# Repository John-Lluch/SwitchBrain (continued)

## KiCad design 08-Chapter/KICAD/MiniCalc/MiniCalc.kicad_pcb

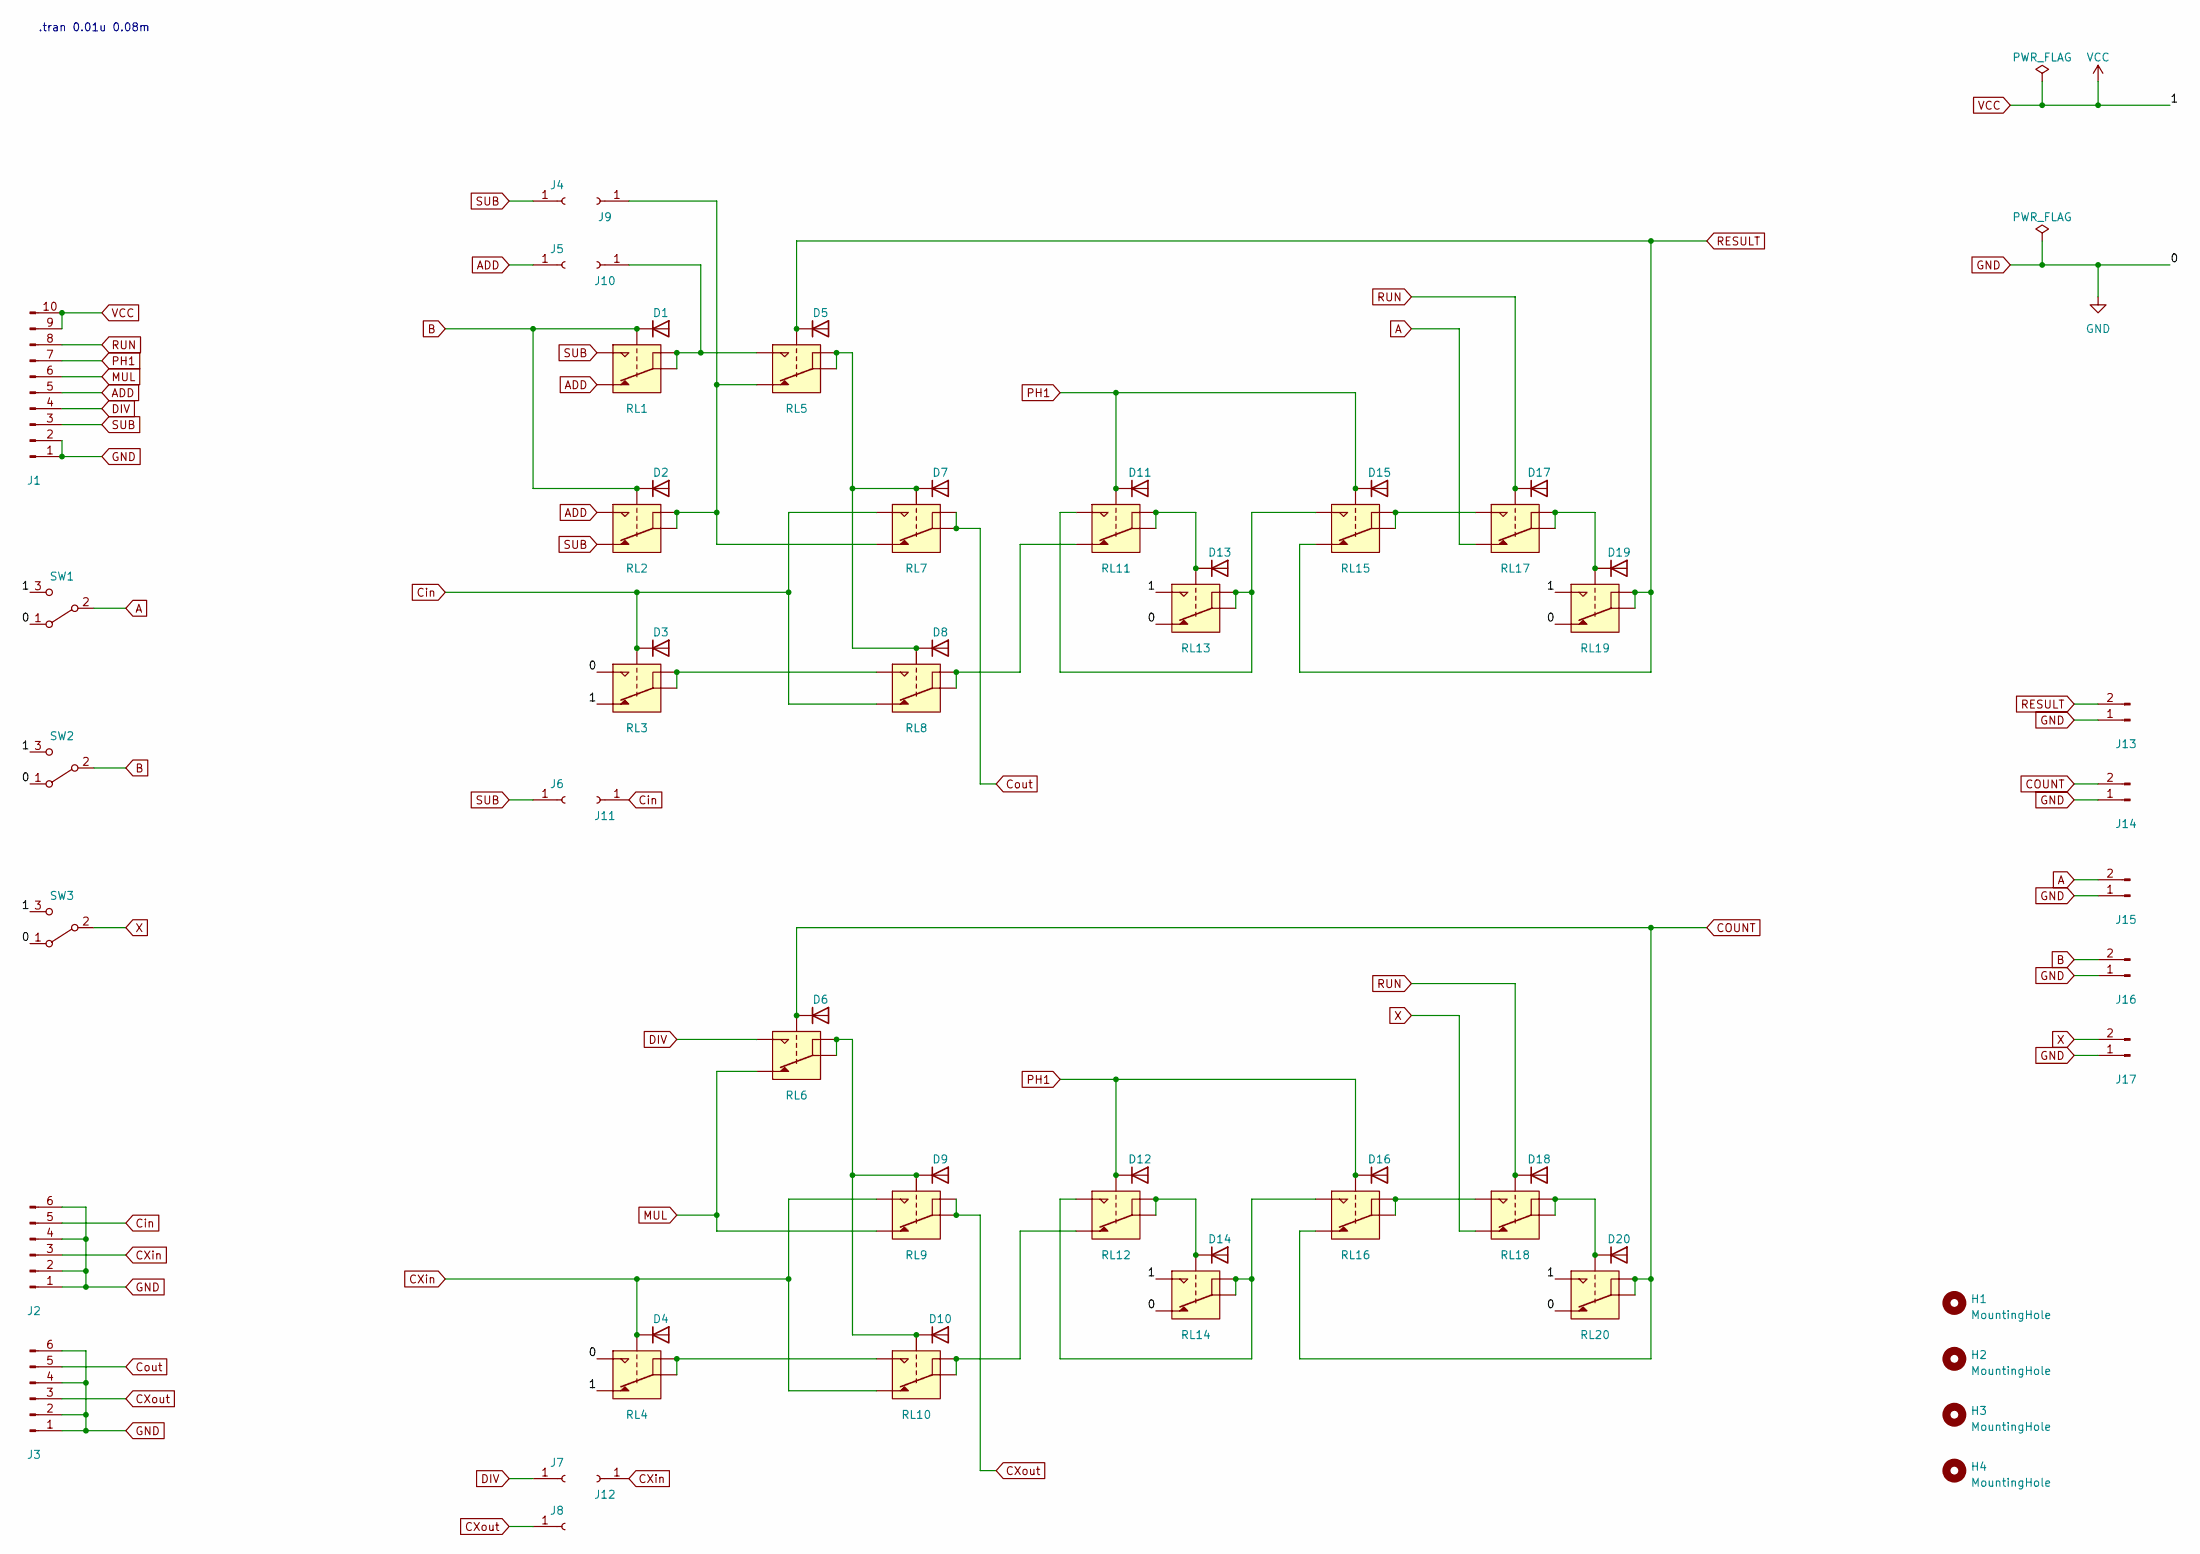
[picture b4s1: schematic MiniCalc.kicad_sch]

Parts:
D1, D2, D3, D4, D5, D6, D7, D8, D9, D10, D11, D12, D13, D14, D15, D16, D17, D18, D19, D20: 1N4007_FLYB; D_A-405_P2.54mm_Vertical_KathodeUp
H1, H2, H3, H4: MountingHole; MountingHole_3.2mm_M3_DIN965_Pad
J1: Conn_01x10_Pin; IDC-Header_2x05_P2.54mm_Horizontal
J2, J3: Conn_01x06_Pin; IDC-Header_2x03_P2.54mm_Horizontal
J4, J5, J6, J7, J8, J9, J10, J11, J12: Conn_01x01_Socket; Pin_D0.7mm_L6.5mm_W1.8mm_FlatFork
J13, J14, J15, J16, J17: Conn_01x02_Pin; JST_XH_S2B-XH-A_1x02_P2.50mm_Horizontal
RL1, RL2, RL3, RL4, RL5, RL6, RL7, RL8, RL9, RL10, RL11, RL12, RL13, RL14, RL15, RL16, RL17, RL18, RL19, RL20: G5V-1; Relay_SPDT_Omron_G5V-1_girat
SW1, SW2, SW3: SW_SPDT; SW_Toggle_SPDT_Horizontal

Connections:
A: J15.2, RL17.1, SW1.2 (B)
ADD: J1.5, J5.1, RL1.1, RL2.10
B: D1.1, D2.1, J16.2, RL1.9, RL2.9, SW2.2 (B)
COUNT: D6.1, J14.2, RL6.9, RL16.1, RL20.5, RL20.6
CXin: D4.1, J2.3, J12.1, RL4.9, RL9.10, RL10.1
CXout: J3.3, J8.1, RL9.5, RL9.6
Cin: D3.1, J2.5, J11.1, RL3.9, RL7.10, RL8.1
Cout: J3.5, RL7.5, RL7.6
DIV: J1.4, J7.1, RL6.10
GND: D1.2 (GND), D2.2 (GND), D3.2 (GND), D4.2 (GND), D5.2 (GND), D6.2 (GND), D7.2 (GND), D8.2 (GND), D9.2 (GND), D10.2 (GND), D11.2 (GND), D12.2 (GND), D13.2 (GND), D14.2 (GND), D15.2 (GND), D16.2 (GND), D17.2 (GND), D18.2 (GND), D19.2 (GND), D20.2 (GND), J1.1, J1.2, J2.1, J2.2, J2.4, J2.6, J3.1, J3.2, J3.4, J3.6, J13.1, J14.1, J15.1, J16.1, J17.1, RL1.2 (GND), RL2.2 (GND), RL3.2 (GND), RL3.10, RL4.2 (GND), RL4.10, RL5.2 (GND), RL6.2 (GND), RL7.2 (GND), RL8.2 (GND), RL9.2 (GND), RL10.2 (GND), RL11.2 (GND), RL12.2 (GND), RL13.1, RL13.2 (GND), RL14.1, RL14.2 (GND), RL15.2 (GND), RL16.2 (GND), RL17.2 (GND), RL18.2 (GND), RL19.1, RL19.2 (GND), RL20.1, RL20.2 (GND), SW1.1 (A), SW2.1 (A), SW3.1 (A)
MUL: J1.6, RL6.1, RL9.1
unnamed: D7.1, D8.1, RL5.5, RL5.6, RL7.9, RL8.9
unnamed: D9.1, D10.1, RL6.5, RL6.6, RL9.9, RL10.9
unnamed: D13.1, RL11.5, RL11.6, RL13.9
unnamed: D14.1, RL12.5, RL12.6, RL14.9
unnamed: D19.1, RL17.5, RL17.6, RL19.9
unnamed: D20.1, RL18.5, RL18.6, RL20.9
unnamed: J9.1, RL2.5, RL2.6, RL5.1, RL7.1
unnamed: J10.1, RL1.5, RL1.6, RL5.10
unnamed: RL3.5, RL3.6, RL8.10
unnamed: RL10.5, RL10.6, RL12.1
unnamed: RL4.5, RL4.6, RL10.10
unnamed: RL8.5, RL8.6, RL11.1
unnamed: RL11.10, RL13.5, RL13.6, RL15.10
unnamed: RL12.10, RL14.5, RL14.6, RL16.10
unnamed: RL15.5, RL15.6, RL17.10
unnamed: RL16.5, RL16.6, RL18.10
PH1: D11.1, D12.1, D15.1, D16.1, J1.7, RL11.9, RL12.9, RL15.9, RL16.9
RESULT: D5.1, J13.2, RL5.9, RL15.1, RL19.5, RL19.6
RUN: D17.1, D18.1, J1.8, RL17.9, RL18.9
SUB: J1.3, J4.1, J6.1, RL1.10, RL2.1
VCC: J1.9, J1.10, RL3.1, RL4.1, RL13.10, RL14.10, RL19.10, RL20.10, SW1.3 (C), SW2.3 (C), SW3.3 (C)
X: J17.2, RL18.1, SW3.2 (B)

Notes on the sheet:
.tran 0.01u 0.08m

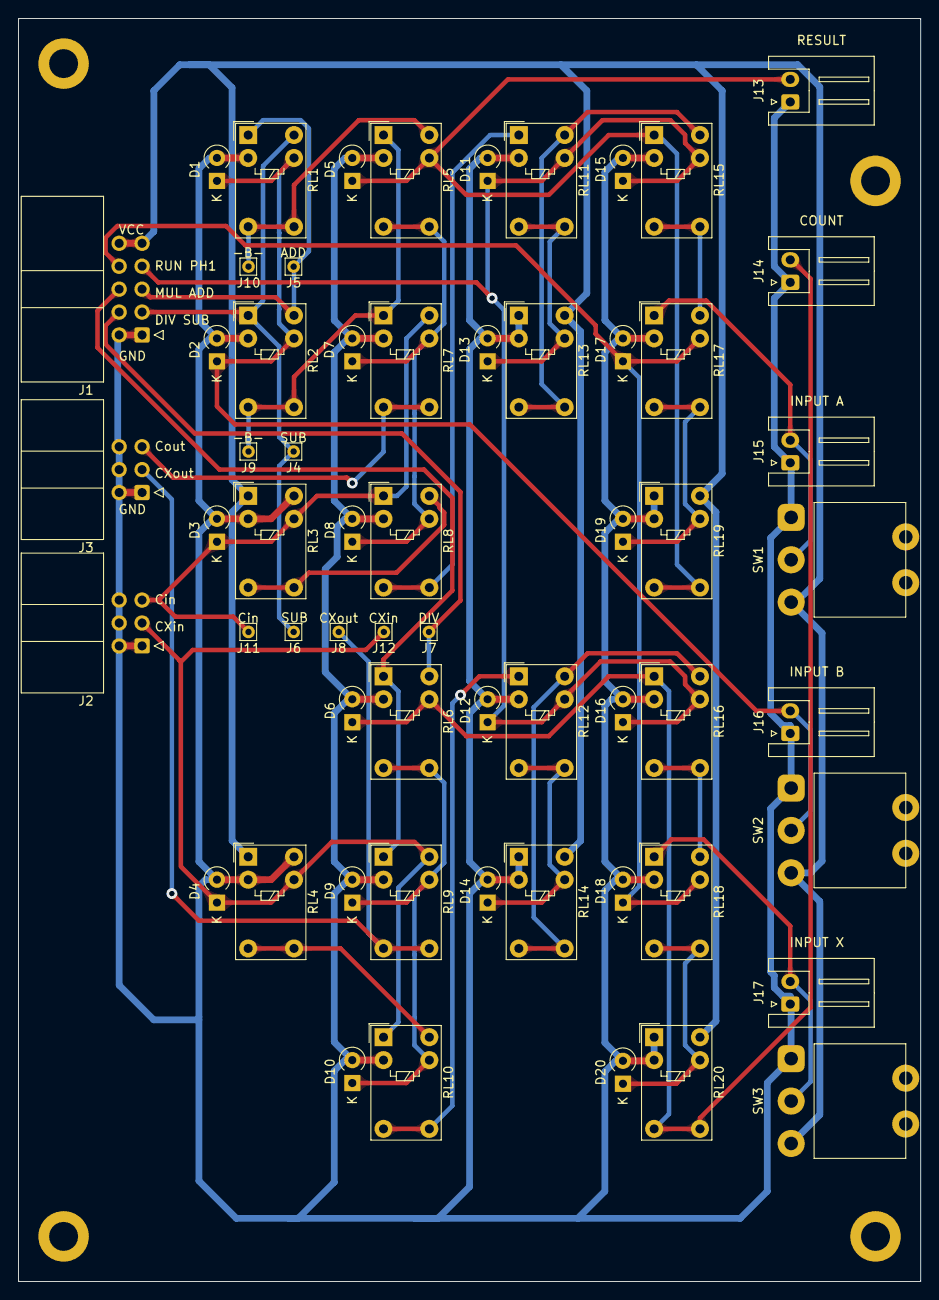
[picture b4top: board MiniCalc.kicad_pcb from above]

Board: 2 copper layers, 100.0 x 140.0 mm, 64 parts (0 on the bottom side), 33 nets.

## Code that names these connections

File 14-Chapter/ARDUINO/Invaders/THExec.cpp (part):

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#include "THExec.h"

// Convenience i/o bit mask defines
#define SBA (1<<DDC6)
#define OE_BA (1<<DDD7)
#define CK_BA (1<<DDE6)
#define RST_AB (1<<DDB4)
#define CK_OEAB (1<<DDB5)
#define CK_AB (1<<DDB6)
#define SEL ((1<<DDB1) | (1<<DDB2) | (1<<DDB3))
#define SEL_Offset DDB1
#define DATA_LO (0x0f)
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#define PORT_DATA_HI PORTF

// Convenience Input Registers (PIN) defines
#define PIN_CK_BA PINE
#define PIN_DATA_LO PIND
#define PIN_DATA_HI PINF

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
// Read CK_BA as input
static inline bool inputCK_BA() {
  return (PIN_CK_BA & CK_BA) != 0;
}

// Output byte to the data port register
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
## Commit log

2023-05-16 Chapter-08
2023-07-16 Renamed Logisim-HD by Logisim-HC
2023-10-11 Chapter 10 files
2024-02-11 Capitulo 12
2024-02-11 Capítulo 12
2024-04-12 Commit Update
2024-04-12 chapter 13
2024-04-14 Add pdf
2024-10-26 Chapter 14
2024-10-28 Add Gerber File
